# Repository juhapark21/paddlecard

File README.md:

# Paddlecard
A badge for Fallout that also acts as a CW paddle!

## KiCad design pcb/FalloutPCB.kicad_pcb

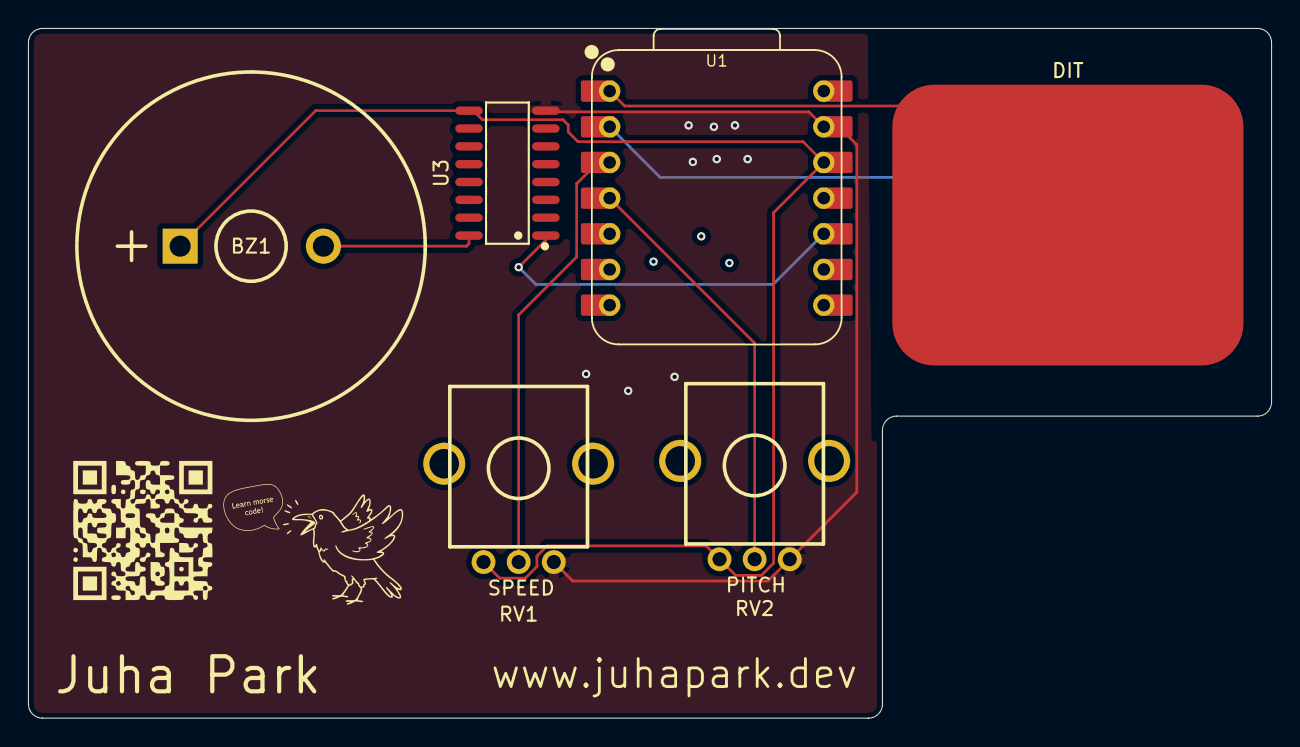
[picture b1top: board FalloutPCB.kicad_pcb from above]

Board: 2 copper layers, 88.5 x 49.1 mm, 7 parts (1 on the bottom side), 8 nets.

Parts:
BZ1: Buzzer; GMC25125YB-42R800
DAH: DAH_PAD; TOUCH_PAD
DIT: DIT_PAD; TOUCH_PAD
RV1: WPM_CTRL; RK09K1130A6S
RV2: PITCH_CTRL; RK09K1130A6S
U1: XIAO-ESP32-S3-DIP; XIAO-ESP32S3-DIP
U3: ULN2003ADR

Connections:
+3V3: BZ1.1 (+), RV1.1, RV2.1, U1.12 (VCC_3V3), U3.9 (COM)
BUZZER_CTRL: U1.10 (GPIO8/D9/A9/MISO), U3.1 (1B)
GND: RV1.3, RV2.3, U1.13 (GND), U3.8 (E)
unnamed: DIT.1 (1_1), U1.1 (GPIO1/D0/A0)
unnamed: DAH.1 (1_1), U1.2 (GPIO2/DA/A1)
OUTPUT: BZ1.2 (-), U3.16 (1C)
PITCH_DATA: RV2.2, U1.4 (GPIO4/D3/A3)
WPM_DATA: RV1.2, U1.3 (GPIO3/D2/A2)
